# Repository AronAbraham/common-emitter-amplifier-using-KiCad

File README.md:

# KiCad Project
I decided to build the BJT circuit and learn about the capacitor's role.
Then I thought, why not design a PCB for this circuit?
The schematic below is what I used to design the PCB.
## Schematic

Be free to spot any error or give any suggestion
## Final Product

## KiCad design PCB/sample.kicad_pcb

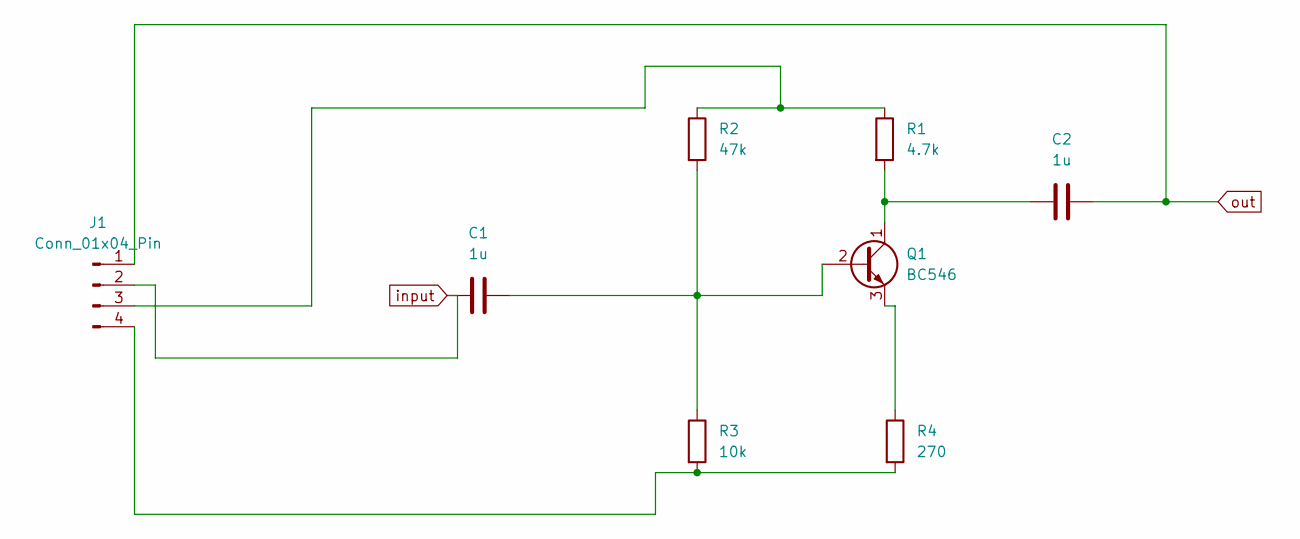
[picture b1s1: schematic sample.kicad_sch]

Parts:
C1, C2: 1u; CP_Radial_D5.0mm_P2.00mm
J1: Conn_01x04_Pin; Molex_Micro-Fit_3.0_43045-0412_2x02_P3.00mm_Vertical
Q1: BC546; TO-92_Inline
R1: 4.7k; R_Axial_DIN0204_L3.6mm_D1.6mm_P7.62mm_Horizontal
R2: 47k; R_Axial_DIN0204_L3.6mm_D1.6mm_P7.62mm_Horizontal
R3: 10k; R_Axial_DIN0204_L3.6mm_D1.6mm_P7.62mm_Horizontal
R4: 270; R_Axial_DIN0204_L3.6mm_D1.6mm_P7.62mm_Horizontal

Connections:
unnamed: J1.3, R1.1, R2.1
unnamed: J1.4, R3.2, R4.2
unnamed: C1.1, Q1.2 (B), R2.2, R3.1
unnamed: C2.2, Q1.1 (C), R1.2
unnamed: Q1.3 (E), R4.1
input: C1.2, J1.2
out: C2.1, J1.1

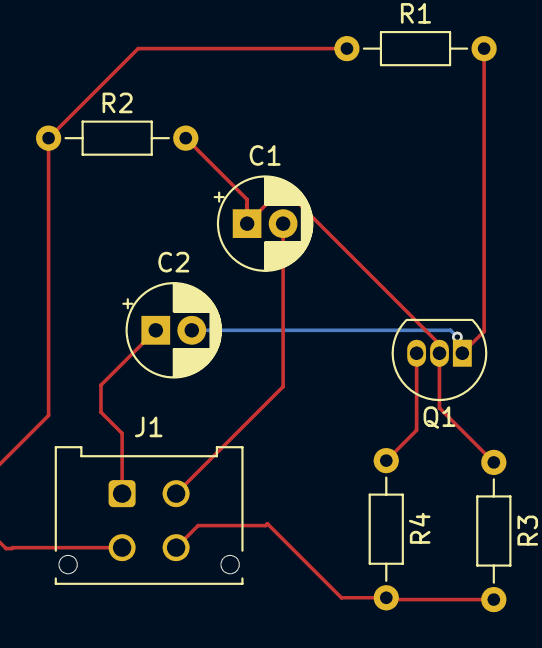
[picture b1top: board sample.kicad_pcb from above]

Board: 2 copper layers, 8 parts (0 on the bottom side), 7 nets.
